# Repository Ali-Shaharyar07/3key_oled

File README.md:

# 3key_oled
A small 3-key macropad with an OLED for my brother.
Each key corresponds to a phrase: "GG", "Ye", "Noice"

---
# Final Product

---

# Design Files

| Schematic | PCB Layout | Case Design |
|----------|------------|-------------|
|  |  |  |

---
# BOM

This is everything I need:

    3x Cherry MX Switches
    3x DSA Keycaps
    4x M3x5x4 Heatset inserts
    4x M3x16mm Screws
    1x 0.91" 128x32 OLED Display
    1x XIAO RP2040
    1x Case (2 printed parts)
    1x PCB
---
# Remarks

It was a fun experience making this hackpad, the 3D design was imo the most difficult, especially trying to get things to line up. 
The OLED pins might be poking into the case, but i'll trim them IRL. 
I'm planning on having the OLED have a cat animation :3

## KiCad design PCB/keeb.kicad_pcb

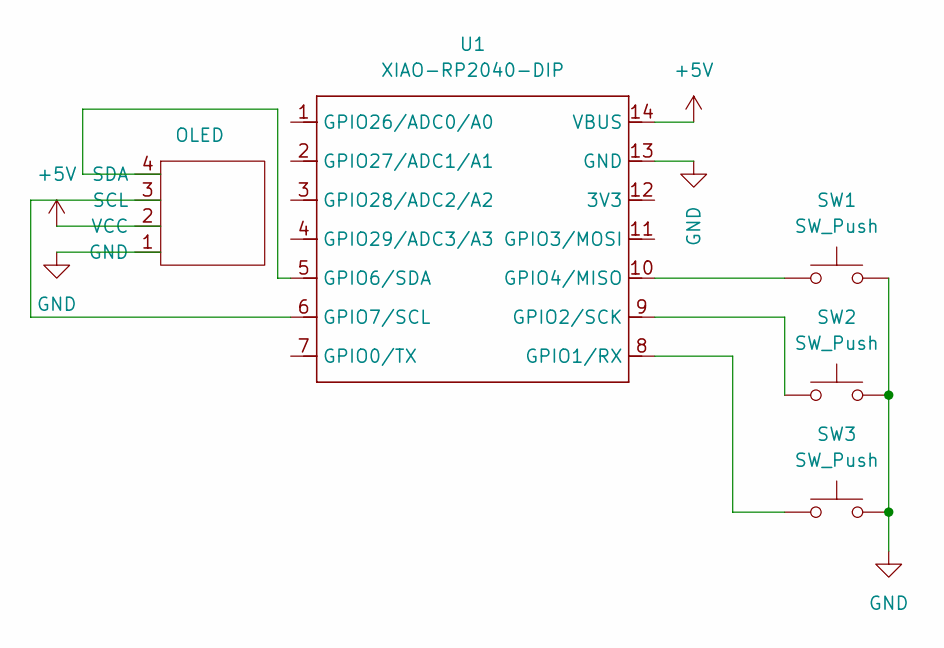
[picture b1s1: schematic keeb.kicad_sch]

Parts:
OLED1: OLED; SSD1306-0.91-OLED-4pin-128x32
SW1, SW2, SW3: SW_Push; SW_Cherry_MX_1.00u_PCB
U1: XIAO-RP2040-DIP

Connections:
+5V: OLED1.2 (VCC), U1.14 (VBUS)
GND: OLED1.1 (GND), SW1.1, SW2.1, SW3.1, U1.13 (GND)
unnamed: OLED1.3 (SCL), U1.6 (GPIO7/SCL)
unnamed: OLED1.4 (SDA), U1.5 (GPIO6/SDA)
unnamed: SW3.2, U1.8 (GPIO1/RX)
unnamed: SW2.2, U1.9 (GPIO2/SCK)
unnamed: SW1.2, U1.10 (GPIO4/MISO)

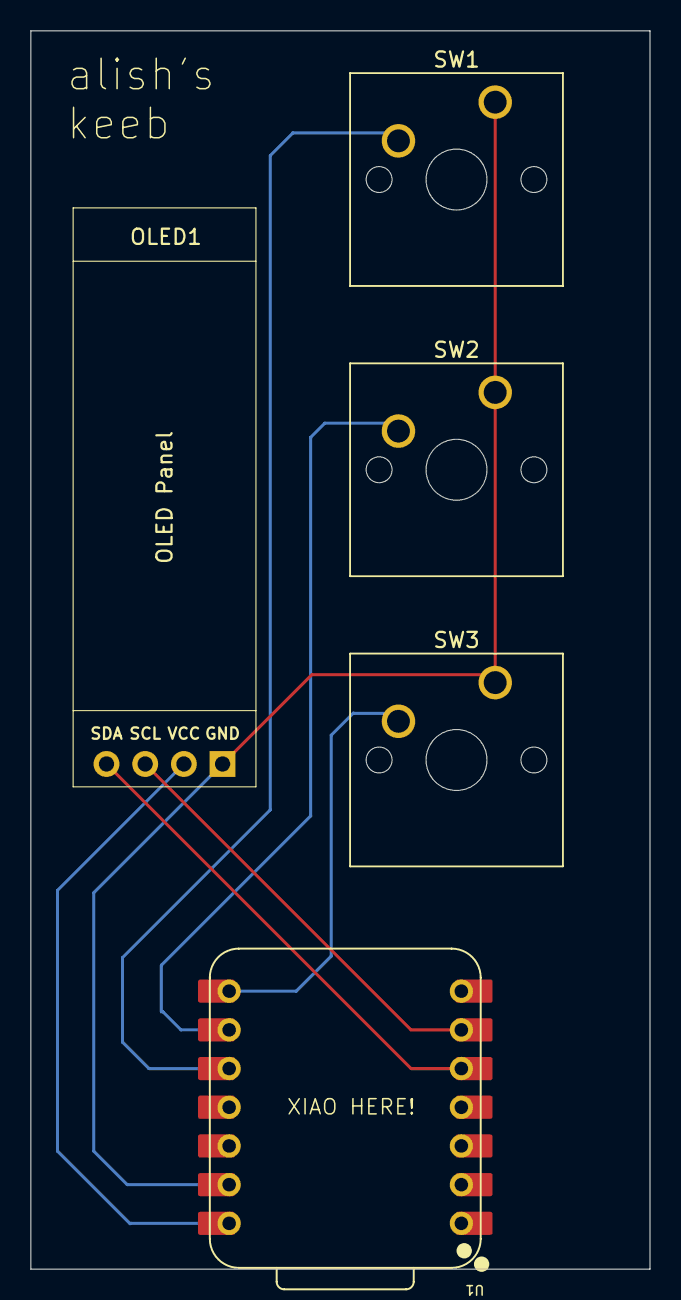
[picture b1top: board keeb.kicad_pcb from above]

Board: 2 copper layers, 40.6 x 81.3 mm, 5 parts (0 on the bottom side), 7 nets.

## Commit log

2025-12-28 3key_oled uploaded for review
2025-12-28 added pics
